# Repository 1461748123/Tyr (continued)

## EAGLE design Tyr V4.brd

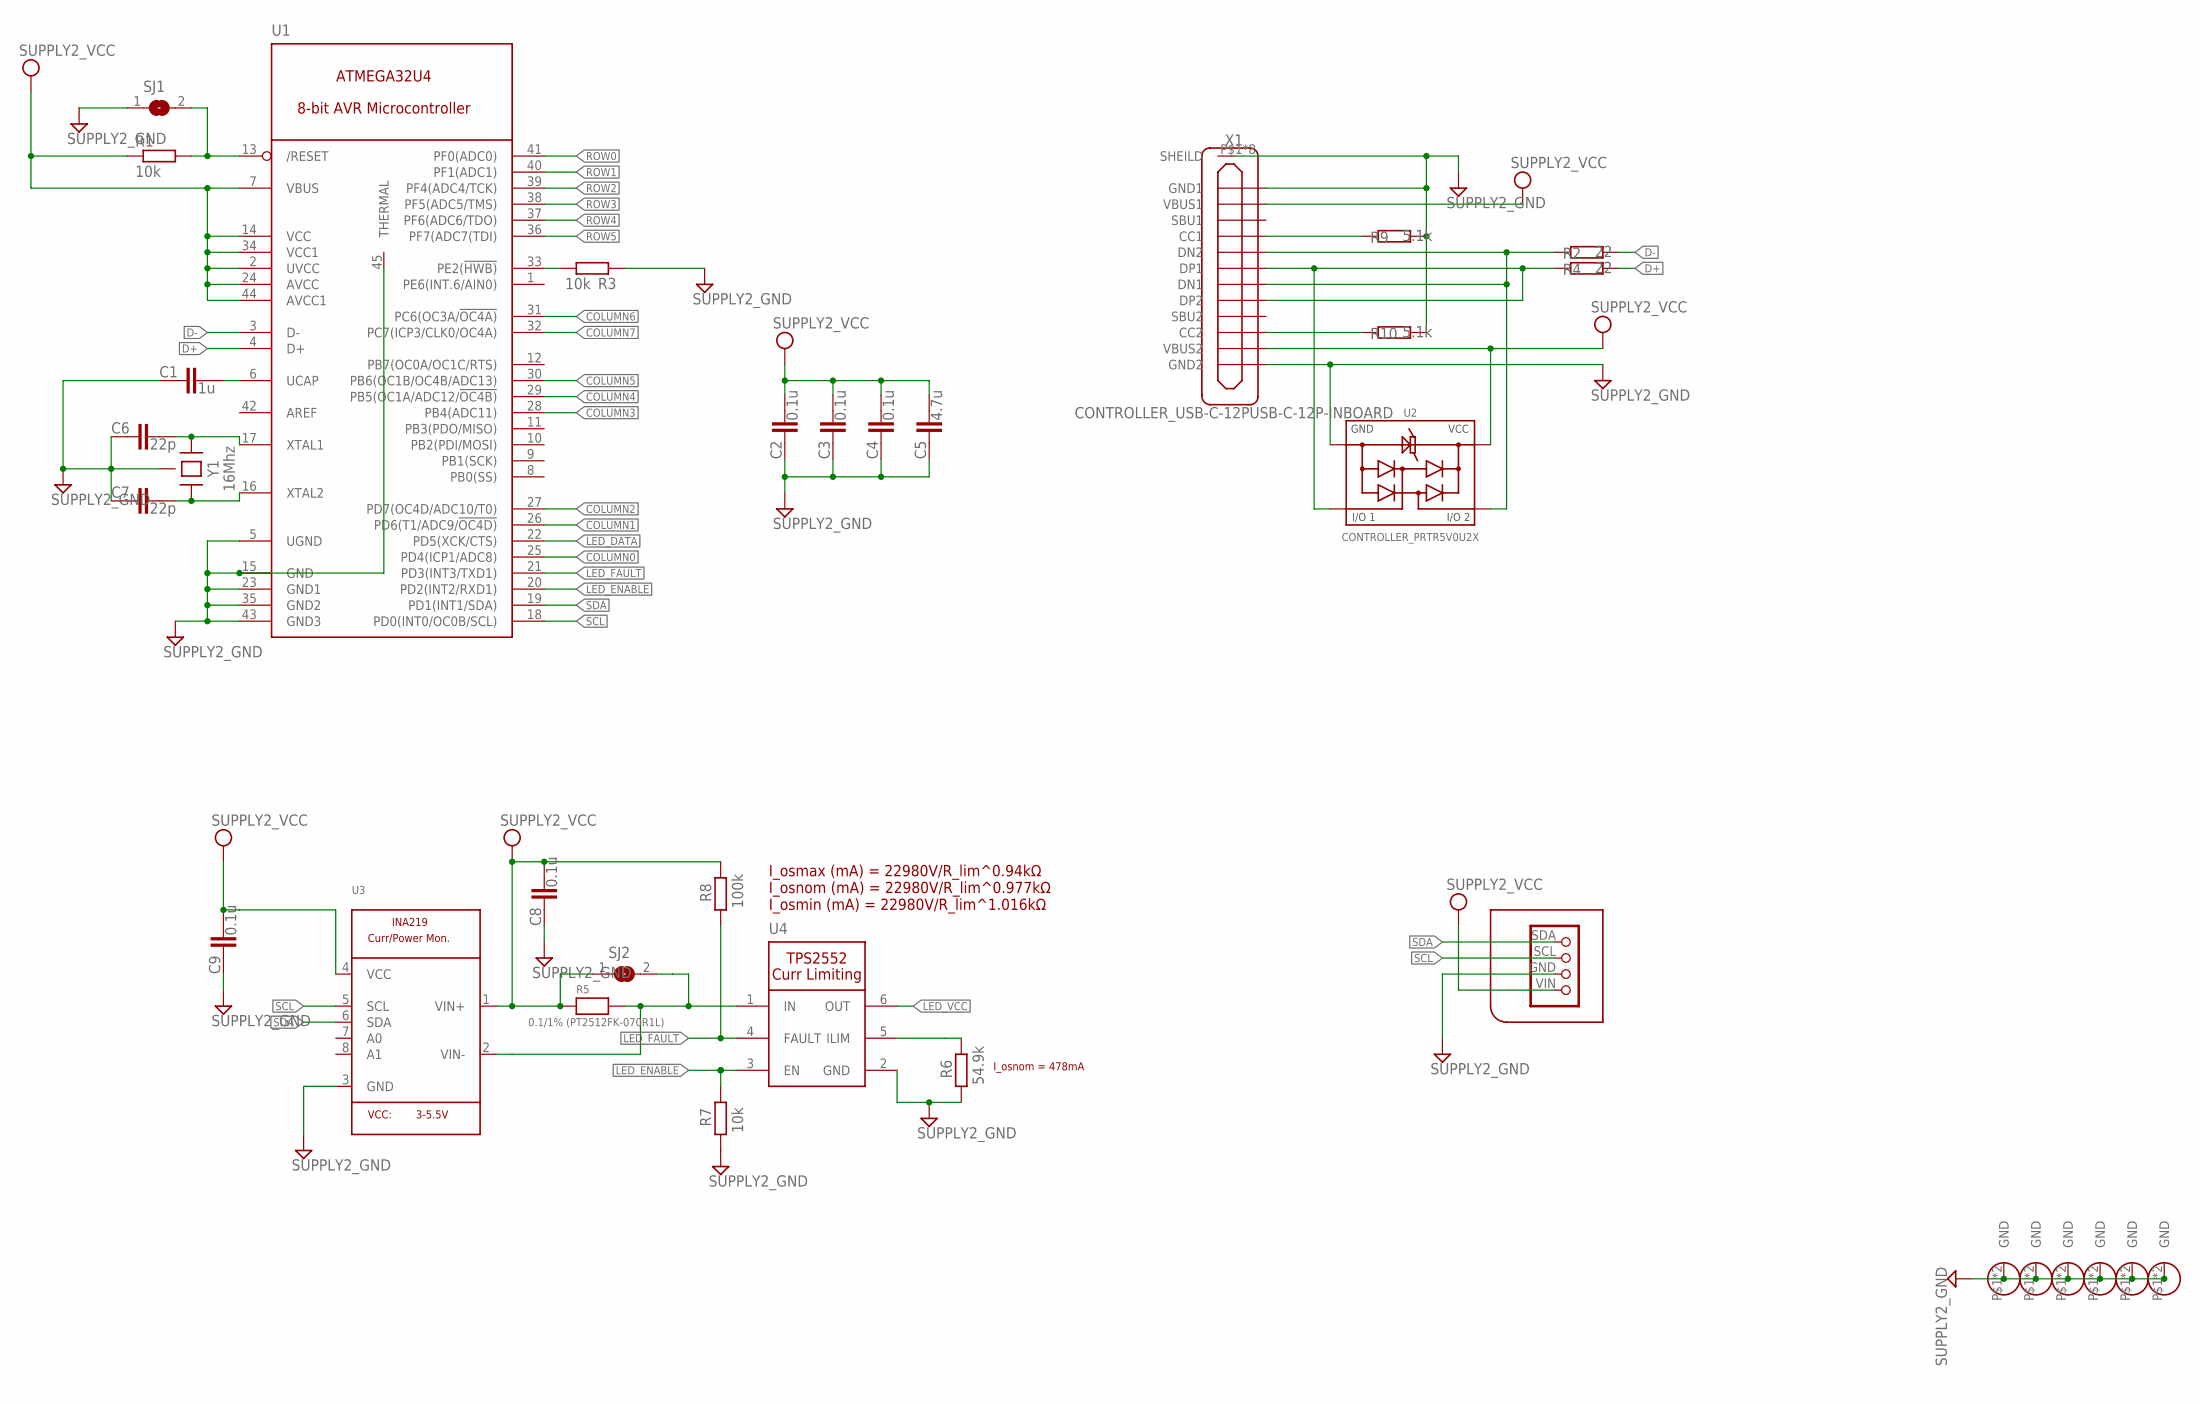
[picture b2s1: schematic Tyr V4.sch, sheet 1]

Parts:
C1: 1u; COMPONENTS_C0603
C2, C3, C4, C8, C9: 0.1u; COMPONENTS_C0603
C5: 4.7u; COMPONENTS_C0603
C6, C7: 22p; COMPONENTS_C0603
HOLE1, HOLE2, HOLE3, HOLE4, HOLE5, HOLE6: HOLE_MOUNT_HOLE; HOLE_M3_OVAL
J1: TYR_TYR_DISPLAY
R1, R3, R7: 10k; COMPONENTS_R0603
R2, R4: 22; COMPONENTS_R0603
R5: 0.1/1% (PT2512FK-070R1L); MICROBUILDER_2512
R6: 54.9k; COMPONENTS_R0603
R8: 100k; COMPONENTS_R0603
R9, R10: 5.1k; COMPONENTS_R0603
SJ1, SJ2: MICROBUILDER_SOLDERJUMPER; MICROBUILDER_SOLDERJUMPER_ARROW_NOPASTE
U1: TYR_ATMEGA32U4; TYR_QFN44-7X7
U2: CONTROLLER_PRTR5V0U2X
U3: MICROBUILDER_INA219; MICROBUILDER_SOT23-8
U4: TYR_TPS2552; TYR_SOT-23-6P
X1: CONTROLLER_USB-C-12PUSB-C-12P-INBOARD; CONTROLLER_USB-C-12P-INBOARD
Y1: 16Mhz; CONTROLLER_CRYSTAL-3.2X2.5

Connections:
COLUMN0: U1.25 (PD4(ICP1/ADC8)); also elsewhere on the board
COLUMN1: U1.26 (PD6(T1/ADC9/!OC4D)); also elsewhere on the board
COLUMN2: U1.27 (PD7(OC4D/ADC10/T0)); also elsewhere on the board
COLUMN3: U1.28 (PB4(ADC11)); also elsewhere on the board
COLUMN4: U1.29 (PB5(OC1A/ADC12/!OC4B)); also elsewhere on the board
COLUMN5: U1.30 (PB6(OC1B/OC4B/ADC13)); also elsewhere on the board
COLUMN6: U1.31 (PC6(OC3A/!OC4A)); also elsewhere on the board
COLUMN7: U1.32 (PC7(ICP3/CLK0/OC4A)); also elsewhere on the board
D+: R4.2, U1.4 (D+)
D-: R2.2, U1.3 (D-)
GND: C1.1, C2.1, C3.1, C4.1, C5.1, C6.1, C7.1, C8.1, C9.1, HOLE1.P$1, HOLE1.P$2, HOLE2.P$1, HOLE2.P$2, HOLE3.P$1, HOLE3.P$2, HOLE4.P$1, HOLE4.P$2, HOLE5.P$1, HOLE5.P$2, HOLE6.P$1, HOLE6.P$2, J1.GND (3), R3.1, R6.1, R7.1, R9.2, R10.2, SJ1.1, U1.5 (UGND), U1.15 (GND), U1.23 (GND1), U1.35 (GND2), U1.43 (GND3), U1.45 (THERMAL), U2.1, U3.3 (GND), U4.2 (GND), X1.GND1, X1.GND2, X1.P$1 (SHEILD), X1.P$2 (SHEILD), X1.P$3 (SHEILD), X1.P$4 (SHEILD), X1.P$5 (SHEILD), X1.P$6 (SHEILD), X1.P$8 (SHEILD), X1.P$9 (SHEILD), Y1.2 (GND), Y1.4 (GND); also elsewhere on the board
LED_DATA: U1.22 (PD5(XCK/CTS)); also elsewhere on the board
LED_ENABLE: R7.2, U1.20 (PD2(INT2/RXD1)), U4.3 (EN)
LED_FAULT: R8.1, U1.21 (PD3(INT3/TXD1)), U4.4 (FAULT)
LED_VCC: U4.6 (OUT); also elsewhere on the board
unnamed: R5.2, SJ2.2, U3.2 (VIN-), U4.1 (IN)
unnamed: R6.2, U4.5 (ILIM)
unnamed: R9.1, X1.CC1
unnamed: R3.2, U1.33 (PE2(!HWB))
unnamed: R2.1, U2.3, X1.DN1, X1.DN2
unnamed: R4.1, U2.2, X1.DP1, X1.DP2
unnamed: C1.2, U1.6 (UCAP)
unnamed: R10.1, X1.CC2
RESET: R1.2, SJ1.2, U1.13 (/RESET)
ROW0: U1.41 (PF0(ADC0)); also elsewhere on the board
ROW1: U1.40 (PF1(ADC1)); also elsewhere on the board
ROW2: U1.39 (PF4(ADC4/TCK)); also elsewhere on the board
ROW3: U1.38 (PF5(ADC5/TMS)); also elsewhere on the board
ROW4: U1.37 (PF6(ADC6/TDO)); also elsewhere on the board
ROW5: U1.36 (PF7(ADC7(TDI)); also elsewhere on the board
SCL: J1.SCL (2), U1.18 (PD0(INT0/OC0B/SCL)), U3.5 (SCL)
SDA: J1.SDA (1), U1.19 (PD1(INT1/SDA)), U3.6 (SDA)
VCC: C2.2, C3.2, C4.2, C5.2, C8.2, C9.2, J1.VIN (4), R1.1, R5.1, R8.2, SJ2.1, U1.2 (UVCC), U1.7 (VBUS), U1.14 (VCC), U1.24 (AVCC), U1.34 (VCC1), U1.44 (AVCC1), U2.4, U3.1 (VIN+), U3.4 (VCC), X1.VBUS1, X1.VBUS2
XTAL1: C6.2, U1.17 (XTAL1), Y1.1
XTAL2: C7.2, U1.16 (XTAL2), Y1.3 (2)

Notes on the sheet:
I_osmax (mA) = 22980V/R_lim^0.94kΩ I_osnom (mA) = 22980V/R_lim^0.977kΩ I_osmin (mA) = 22980V/R_lim^1.016kΩ
I_osnom = 478mA

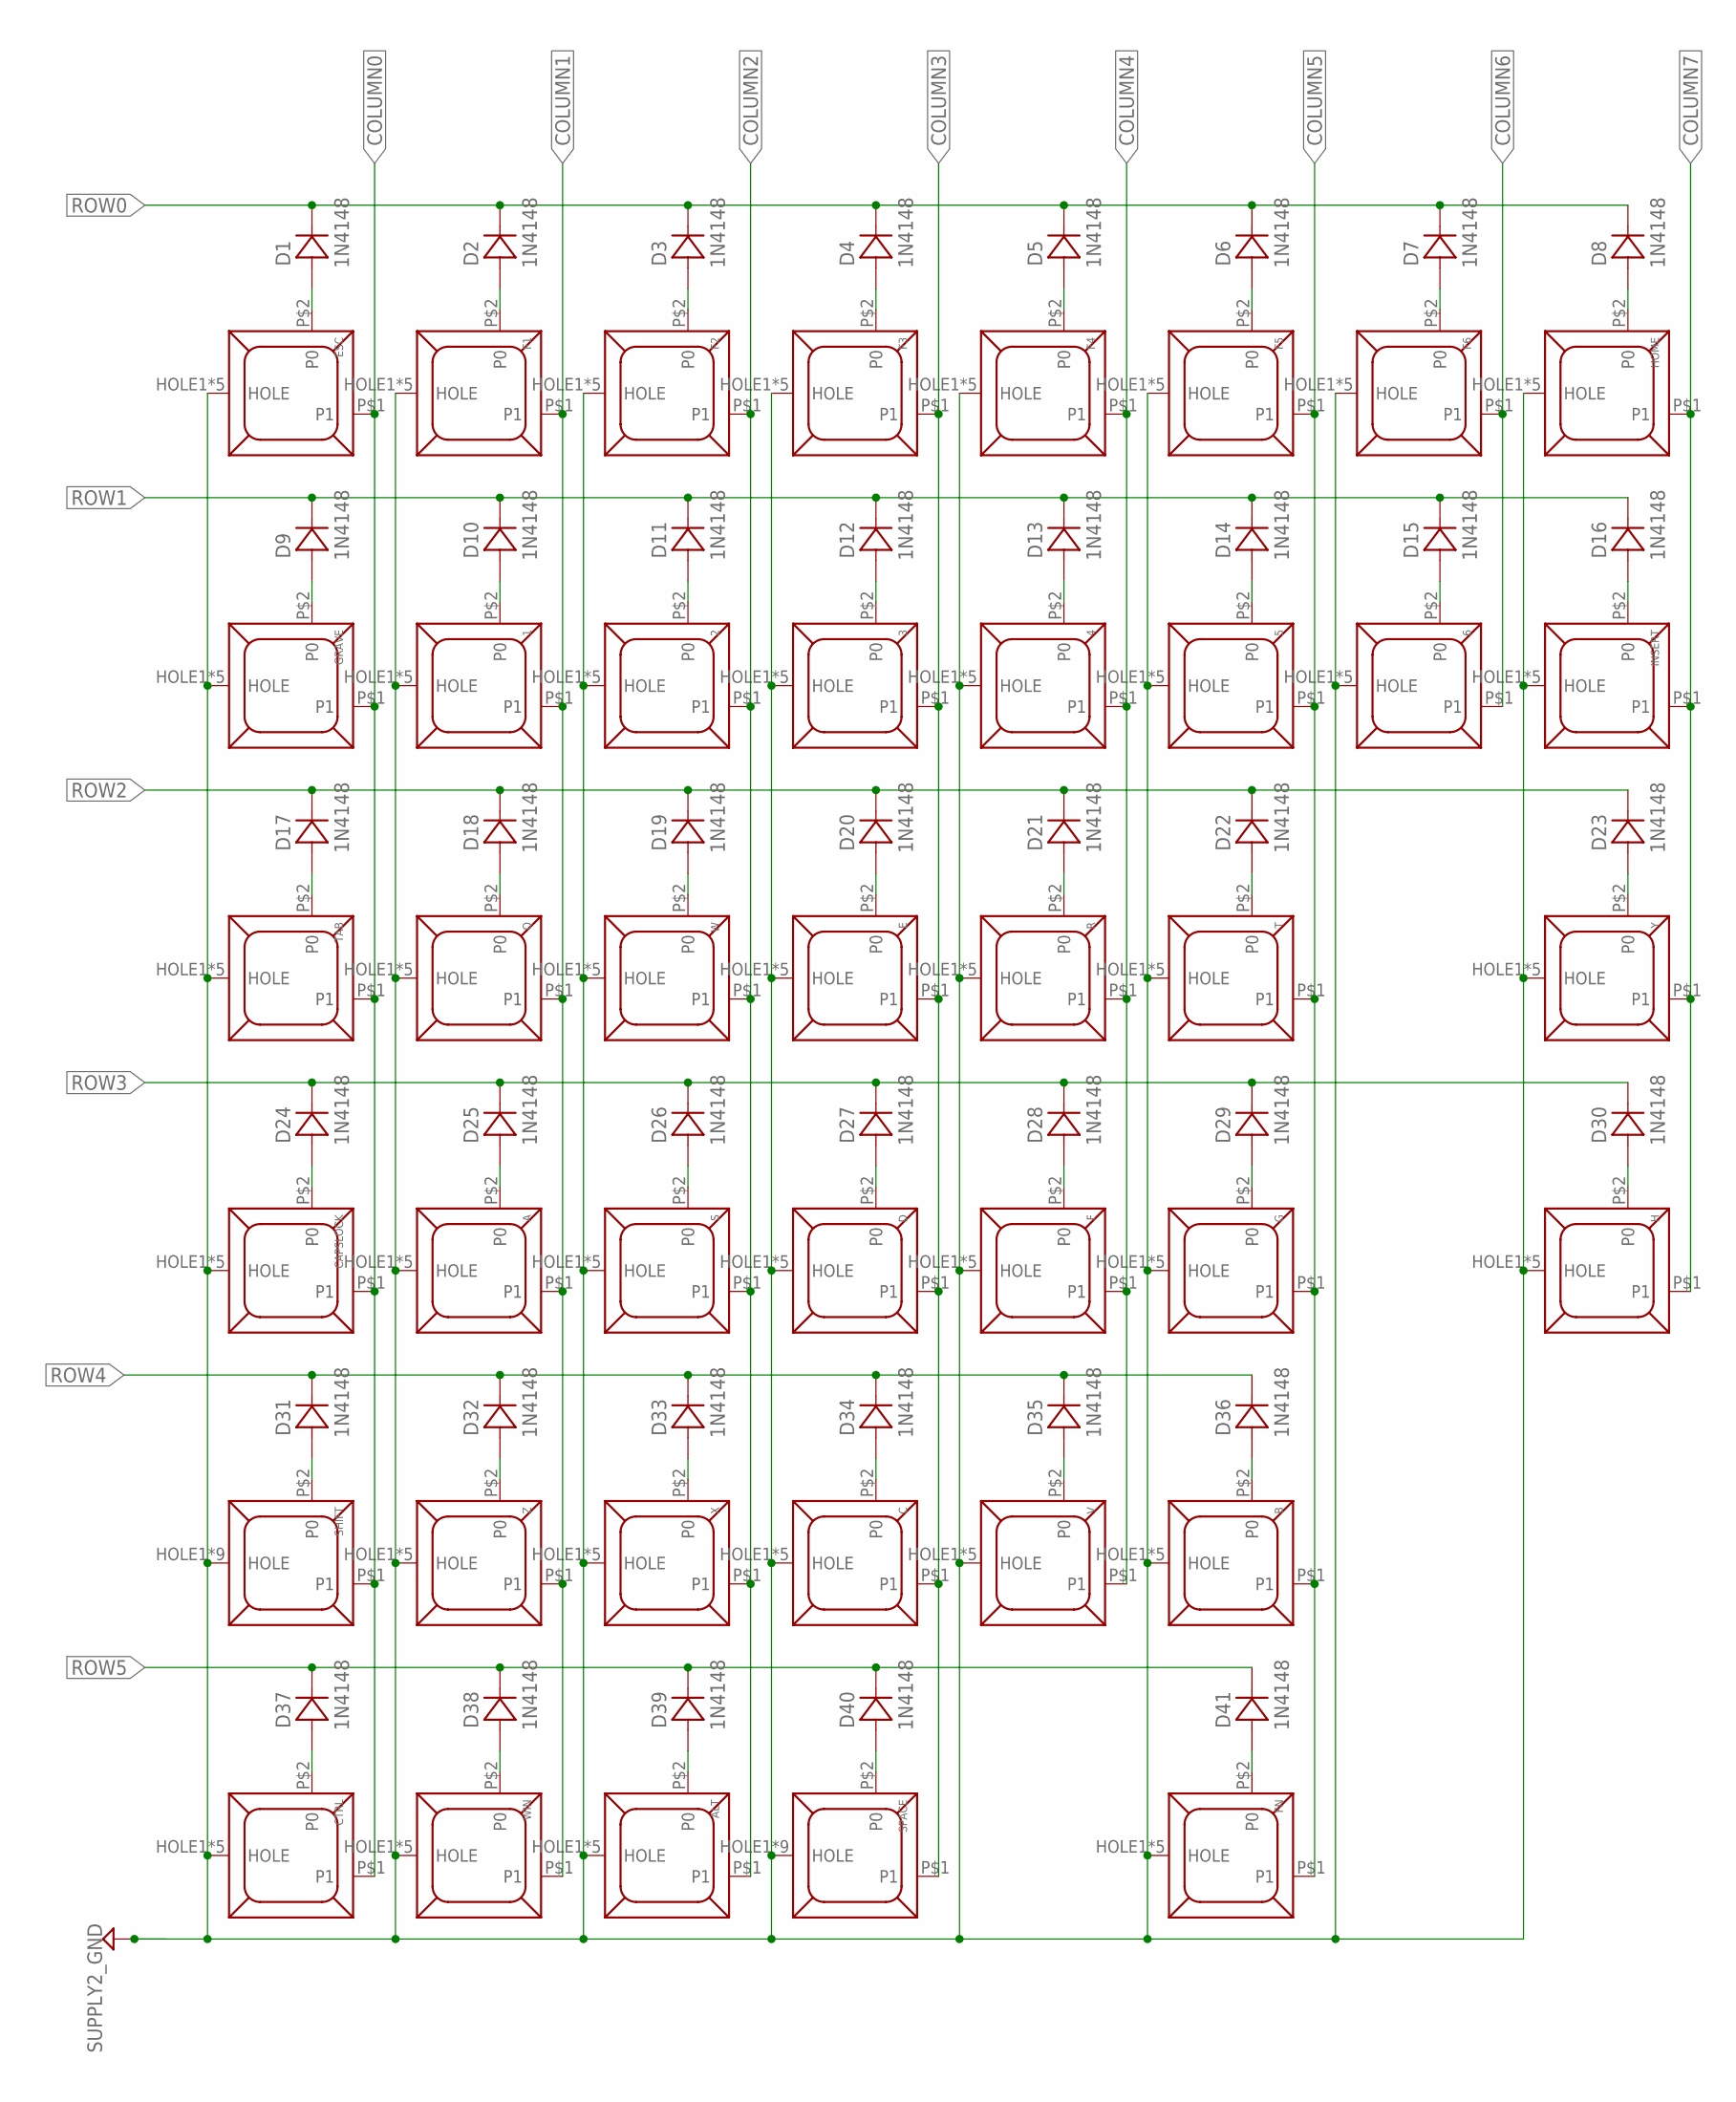
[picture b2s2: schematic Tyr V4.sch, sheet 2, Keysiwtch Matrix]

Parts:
1, 2, 3, 4, 5, 6: KEYBOARD_KEYSWITCH-MX-1U-HOTSWAP; KEYBOARD_MX-1U-HOTSWAP
A: KEYBOARD_KEYSWITCH-MX-1U-HOTSWAP; KEYBOARD_MX-1U-HOTSWAP
ALT: KEYBOARD_KEYSWITCH-MX-1U-HOTSWAP; KEYBOARD_MX-1U-HOTSWAP
B: KEYBOARD_KEYSWITCH-MX-1U-HOTSWAP; KEYBOARD_MX-1U-HOTSWAP
C: KEYBOARD_KEYSWITCH-MX-1U-HOTSWAP; KEYBOARD_MX-1U-HOTSWAP
CAPSLOCK: KEYBOARD_KEYSWITCH-MX-1U-HOTSWAPCAPSLOCK; KEYBOARD_MX-1U-HOTSWAP-CAPSLOCK
CTRL: KEYBOARD_KEYSWITCH-MX-1U-HOTSWAP; KEYBOARD_MX-1U-HOTSWAP
D: KEYBOARD_KEYSWITCH-MX-1U-HOTSWAP; KEYBOARD_MX-1U-HOTSWAP
D1, D2, D3, D4, D5, D6, D7, D8, D9, D10, D11, D12, D13, D14, D15, D16, D17, D18, D19, D20, D21, D22, D23, D24, D25, D26, D27, D28, D29, D30, D31, D32, D33, D34, D35, D36, D37, D38, D39, D40, D41: 1N4148; COMPONENTS_SOD-123
E: KEYBOARD_KEYSWITCH-MX-1U-HOTSWAP; KEYBOARD_MX-1U-HOTSWAP
ESC: KEYBOARD_KEYSWITCH-MX-1U-HOTSWAP; KEYBOARD_MX-1U-HOTSWAP
F, F1, F2, F3, F4, F5, F6: KEYBOARD_KEYSWITCH-MX-1U-HOTSWAP; KEYBOARD_MX-1U-HOTSWAP
FN: KEYBOARD_KEYSWITCH-MX-1U-HOTSWAP; KEYBOARD_MX-1U-HOTSWAP
G: KEYBOARD_KEYSWITCH-MX-1U-HOTSWAP; KEYBOARD_MX-1U-HOTSWAP
GRAVE: KEYBOARD_KEYSWITCH-MX-1U-HOTSWAP; KEYBOARD_MX-1U-HOTSWAP
H: KEYBOARD_KEYSWITCH-MX-1U-HOTSWAP; KEYBOARD_MX-1U-HOTSWAP
HOME: KEYBOARD_KEYSWITCH-MX-1U-HOTSWAP; KEYBOARD_MX-1U-HOTSWAP
INSERT: KEYBOARD_KEYSWITCH-MX-1U-HOTSWAP; KEYBOARD_MX-1U-HOTSWAP
Q: KEYBOARD_KEYSWITCH-MX-1U-HOTSWAP; KEYBOARD_MX-1U-HOTSWAP
R: KEYBOARD_KEYSWITCH-MX-1U-HOTSWAP; KEYBOARD_MX-1U-HOTSWAP
S: KEYBOARD_KEYSWITCH-MX-1U-HOTSWAP; KEYBOARD_MX-1U-HOTSWAP
SHIFT: KEYBOARD_KEYSWITCH-MX-2U-HOTSWAP; KEYBOARD_MX-2U-HOTSWAP
SPACE: KEYBOARD_KEYSWITCH-MX-2U-HOTSWAP; KEYBOARD_MX-2U-HOTSWAP
T: KEYBOARD_KEYSWITCH-MX-1U-HOTSWAP; KEYBOARD_MX-1U-HOTSWAP
TAB: KEYBOARD_KEYSWITCH-MX-1U-HOTSWAP; KEYBOARD_MX-1U-HOTSWAP
V: KEYBOARD_KEYSWITCH-MX-1U-HOTSWAP; KEYBOARD_MX-1U-HOTSWAP
W: KEYBOARD_KEYSWITCH-MX-1U-HOTSWAP; KEYBOARD_MX-1U-HOTSWAP
WIN: KEYBOARD_KEYSWITCH-MX-1U-HOTSWAP; KEYBOARD_MX-1U-HOTSWAP
X: KEYBOARD_KEYSWITCH-MX-1U-HOTSWAP; KEYBOARD_MX-1U-HOTSWAP
Y: KEYBOARD_KEYSWITCH-MX-1U-HOTSWAP; KEYBOARD_MX-1U-HOTSWAP
Z: KEYBOARD_KEYSWITCH-MX-1U-HOTSWAP; KEYBOARD_MX-1U-HOTSWAP

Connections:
COLUMN0: CAPSLOCK.P$1 (P1), CTRL.P$1 (P1), ESC.P$1 (P1), GRAVE.P$1 (P1), SHIFT.P$1 (P1), TAB.P$1 (P1); also elsewhere on the board
COLUMN1: 1.P$1 (P1), A.P$1 (P1), F1.P$1 (P1), Q.P$1 (P1), WIN.P$1 (P1), Z.P$1 (P1); also elsewhere on the board
COLUMN2: 2.P$1 (P1), ALT.P$1 (P1), F2.P$1 (P1), S.P$1 (P1), W.P$1 (P1), X.P$1 (P1); also elsewhere on the board
COLUMN3: 3.P$1 (P1), C.P$1 (P1), D.P$1 (P1), E.P$1 (P1), F3.P$1 (P1), SPACE.P$1 (P1); also elsewhere on the board
COLUMN4: 4.P$1 (P1), F.P$1 (P1), F4.P$1 (P1), R.P$1 (P1), V.P$1 (P1); also elsewhere on the board
COLUMN5: 5.P$1 (P1), B.P$1 (P1), F5.P$1 (P1), FN.P$1 (P1), G.P$1 (P1), T.P$1 (P1); also elsewhere on the board
COLUMN6: 6.P$1 (P1), F6.P$1 (P1); also elsewhere on the board
COLUMN7: H.P$1 (P1), HOME.P$1 (P1), INSERT.P$1 (P1), Y.P$1 (P1); also elsewhere on the board
GND: 1.HOLE1 (HOLE), 1.HOLE2 (HOLE), 1.HOLE3 (HOLE), 1.HOLE4 (HOLE), 1.HOLE5 (HOLE), 2.HOLE1 (HOLE), 2.HOLE2 (HOLE), 2.HOLE3 (HOLE), 2.HOLE4 (HOLE), 2.HOLE5 (HOLE), 3.HOLE1 (HOLE), 3.HOLE2 (HOLE), 3.HOLE3 (HOLE), 3.HOLE4 (HOLE), 3.HOLE5 (HOLE), 4.HOLE1 (HOLE), 4.HOLE2 (HOLE), 4.HOLE3 (HOLE), 4.HOLE4 (HOLE), 4.HOLE5 (HOLE), 5.HOLE1 (HOLE), 5.HOLE2 (HOLE), 5.HOLE3 (HOLE), 5.HOLE4 (HOLE), 5.HOLE5 (HOLE), 6.HOLE1 (HOLE), 6.HOLE2 (HOLE), 6.HOLE3 (HOLE), 6.HOLE4 (HOLE), 6.HOLE5 (HOLE), A.HOLE1 (HOLE), A.HOLE2 (HOLE), A.HOLE3 (HOLE), A.HOLE4 (HOLE), A.HOLE5 (HOLE), ALT.HOLE1 (HOLE), ALT.HOLE2 (HOLE), ALT.HOLE3 (HOLE), ALT.HOLE4 (HOLE), ALT.HOLE5 (HOLE), B.HOLE1 (HOLE), B.HOLE2 (HOLE), B.HOLE3 (HOLE), B.HOLE4 (HOLE), B.HOLE5 (HOLE), C.HOLE1 (HOLE), C.HOLE2 (HOLE), C.HOLE3 (HOLE), C.HOLE4 (HOLE), C.HOLE5 (HOLE), CAPSLOCK.HOLE1 (HOLE), CAPSLOCK.HOLE2 (HOLE), CAPSLOCK.HOLE3 (HOLE), CAPSLOCK.HOLE4 (HOLE), CAPSLOCK.HOLE5 (HOLE), CTRL.HOLE1 (HOLE), CTRL.HOLE2 (HOLE), CTRL.HOLE3 (HOLE), CTRL.HOLE4 (HOLE), CTRL.HOLE5 (HOLE), D.HOLE1 (HOLE), D.HOLE2 (HOLE), D.HOLE3 (HOLE), D.HOLE4 (HOLE), D.HOLE5 (HOLE), E.HOLE1 (HOLE), E.HOLE2 (HOLE), E.HOLE3 (HOLE), E.HOLE4 (HOLE), E.HOLE5 (HOLE), ESC.HOLE1 (HOLE), ESC.HOLE2 (HOLE), ESC.HOLE3 (HOLE), ESC.HOLE4 (HOLE), ESC.HOLE5 (HOLE), F.HOLE1 (HOLE), F.HOLE2 (HOLE), F.HOLE3 (HOLE), F.HOLE4 (HOLE), F.HOLE5 (HOLE), F1.HOLE1 (HOLE), F1.HOLE2 (HOLE), F1.HOLE3 (HOLE), F1.HOLE4 (HOLE), F1.HOLE5 (HOLE), F2.HOLE1 (HOLE), F2.HOLE2 (HOLE), F2.HOLE3 (HOLE), F2.HOLE4 (HOLE), F2.HOLE5 (HOLE), F3.HOLE1 (HOLE), F3.HOLE2 (HOLE), F3.HOLE3 (HOLE), F3.HOLE4 (HOLE), F3.HOLE5 (HOLE), F4.HOLE1 (HOLE), F4.HOLE2 (HOLE), F4.HOLE3 (HOLE), F4.HOLE4 (HOLE), F4.HOLE5 (HOLE), F5.HOLE1 (HOLE), F5.HOLE2 (HOLE), F5.HOLE3 (HOLE), F5.HOLE4 (HOLE), F5.HOLE5 (HOLE), F6.HOLE1 (HOLE), F6.HOLE2 (HOLE), F6.HOLE3 (HOLE), F6.HOLE4 (HOLE), F6.HOLE5 (HOLE), FN.HOLE1 (HOLE), FN.HOLE2 (HOLE), FN.HOLE3 (HOLE), FN.HOLE4 (HOLE), FN.HOLE5 (HOLE), G.HOLE1 (HOLE), G.HOLE2 (HOLE), G.HOLE3 (HOLE), G.HOLE4 (HOLE), G.HOLE5 (HOLE), GRAVE.HOLE1 (HOLE), GRAVE.HOLE2 (HOLE), GRAVE.HOLE3 (HOLE), GRAVE.HOLE4 (HOLE), GRAVE.HOLE5 (HOLE), H.HOLE1 (HOLE), H.HOLE2 (HOLE), H.HOLE3 (HOLE), H.HOLE4 (HOLE), H.HOLE5 (HOLE), HOME.HOLE1 (HOLE), HOME.HOLE2 (HOLE), HOME.HOLE3 (HOLE), HOME.HOLE4 (HOLE), HOME.HOLE5 (HOLE), INSERT.HOLE1 (HOLE), INSERT.HOLE2 (HOLE), INSERT.HOLE3 (HOLE), INSERT.HOLE4 (HOLE), INSERT.HOLE5 (HOLE), Q.HOLE1 (HOLE), Q.HOLE2 (HOLE), Q.HOLE3 (HOLE), Q.HOLE4 (HOLE), Q.HOLE5 (HOLE), R.HOLE1 (HOLE), R.HOLE2 (HOLE), R.HOLE3 (HOLE), R.HOLE4 (HOLE), R.HOLE5 (HOLE), S.HOLE1 (HOLE), S.HOLE2 (HOLE), S.HOLE3 (HOLE), S.HOLE4 (HOLE), S.HOLE5 (HOLE), SHIFT.HOLE1 (HOLE), SHIFT.HOLE2 (HOLE), SHIFT.HOLE3 (HOLE), SHIFT.HOLE4 (HOLE), SHIFT.HOLE5 (HOLE), SHIFT.HOLE6 (HOLE), SHIFT.HOLE7 (HOLE), SHIFT.HOLE8 (HOLE), SHIFT.HOLE9 (HOLE), SPACE.HOLE1 (HOLE), SPACE.HOLE2 (HOLE), SPACE.HOLE3 (HOLE), SPACE.HOLE4 (HOLE), SPACE.HOLE5 (HOLE), SPACE.HOLE6 (HOLE), SPACE.HOLE7 (HOLE), SPACE.HOLE8 (HOLE), SPACE.HOLE9 (HOLE), T.HOLE1 (HOLE), T.HOLE2 (HOLE), T.HOLE3 (HOLE), T.HOLE4 (HOLE), T.HOLE5 (HOLE), TAB.HOLE1 (HOLE), TAB.HOLE2 (HOLE), TAB.HOLE3 (HOLE), TAB.HOLE4 (HOLE), TAB.HOLE5 (HOLE), V.HOLE1 (HOLE), V.HOLE2 (HOLE), V.HOLE3 (HOLE), V.HOLE4 (HOLE), V.HOLE5 (HOLE), W.HOLE1 (HOLE), W.HOLE2 (HOLE), W.HOLE3 (HOLE), W.HOLE4 (HOLE), W.HOLE5 (HOLE), WIN.HOLE1 (HOLE), WIN.HOLE2 (HOLE), WIN.HOLE3 (HOLE), WIN.HOLE4 (HOLE), WIN.HOLE5 (HOLE), X.HOLE1 (HOLE), X.HOLE2 (HOLE), X.HOLE3 (HOLE), X.HOLE4 (HOLE), X.HOLE5 (HOLE), Y.HOLE1 (HOLE), Y.HOLE2 (HOLE), Y.HOLE3 (HOLE), Y.HOLE4 (HOLE), Y.HOLE5 (HOLE), Z.HOLE1 (HOLE), Z.HOLE2 (HOLE), Z.HOLE3 (HOLE), Z.HOLE4 (HOLE), Z.HOLE5 (HOLE); also elsewhere on the board
unnamed: 1.P$2 (P0), D10.A
unnamed: D1.A, ESC.P$2 (P0)
unnamed: D2.A, F1.P$2 (P0)
unnamed: D3.A, F2.P$2 (P0)
unnamed: D4.A, F3.P$2 (P0)
unnamed: D5.A, F4.P$2 (P0)
unnamed: D6.A, F5.P$2 (P0)
unnamed: D7.A, F6.P$2 (P0)
unnamed: D8.A, HOME.P$2 (P0)
unnamed: D16.A, INSERT.P$2 (P0)
unnamed: 6.P$2 (P0), D15.A
unnamed: 5.P$2 (P0), D14.A
unnamed: 4.P$2 (P0), D13.A
unnamed: 3.P$2 (P0), D12.A
unnamed: 2.P$2 (P0), D11.A
unnamed: D9.A, GRAVE.P$2 (P0)
unnamed: D23.A, Y.P$2 (P0)
unnamed: D22.A, T.P$2 (P0)
unnamed: D21.A, R.P$2 (P0)
unnamed: D20.A, E.P$2 (P0)
unnamed: D19.A, W.P$2 (P0)
unnamed: D17.A, TAB.P$2 (P0)
unnamed: CAPSLOCK.P$2 (P0), D24.A
unnamed: A.P$2 (P0), D25.A
unnamed: D26.A, S.P$2 (P0)
unnamed: D.P$2 (P0), D27.A
unnamed: D28.A, F.P$2 (P0)
unnamed: D29.A, G.P$2 (P0)
unnamed: D30.A, H.P$2 (P0)
unnamed: B.P$2 (P0), D36.A
unnamed: C.P$2 (P0), D34.A
unnamed: D33.A, X.P$2 (P0)
unnamed: D32.A, Z.P$2 (P0)
unnamed: D31.A, SHIFT.P$2 (P0)
unnamed: CTRL.P$2 (P0), D37.A
unnamed: D38.A, WIN.P$2 (P0)
unnamed: ALT.P$2 (P0), D39.A
unnamed: D40.A, SPACE.P$2 (P0)
unnamed: D41.A, FN.P$2 (P0)
unnamed: D35.A, V.P$2 (P0)
unnamed: D18.A, Q.P$2 (P0)
ROW0: D1.C, D2.C, D3.C, D4.C, D5.C, D6.C, D7.C, D8.C; also elsewhere on the board
ROW1: D9.C, D10.C, D11.C, D12.C, D13.C, D14.C, D15.C, D16.C; also elsewhere on the board
ROW2: D17.C, D18.C, D19.C, D20.C, D21.C, D22.C, D23.C; also elsewhere on the board
ROW3: D24.C, D25.C, D26.C, D27.C, D28.C, D29.C, D30.C; also elsewhere on the board
ROW4: D31.C, D32.C, D33.C, D34.C, D35.C, D36.C; also elsewhere on the board
ROW5: D37.C, D38.C, D39.C, D40.C, D41.C; also elsewhere on the board

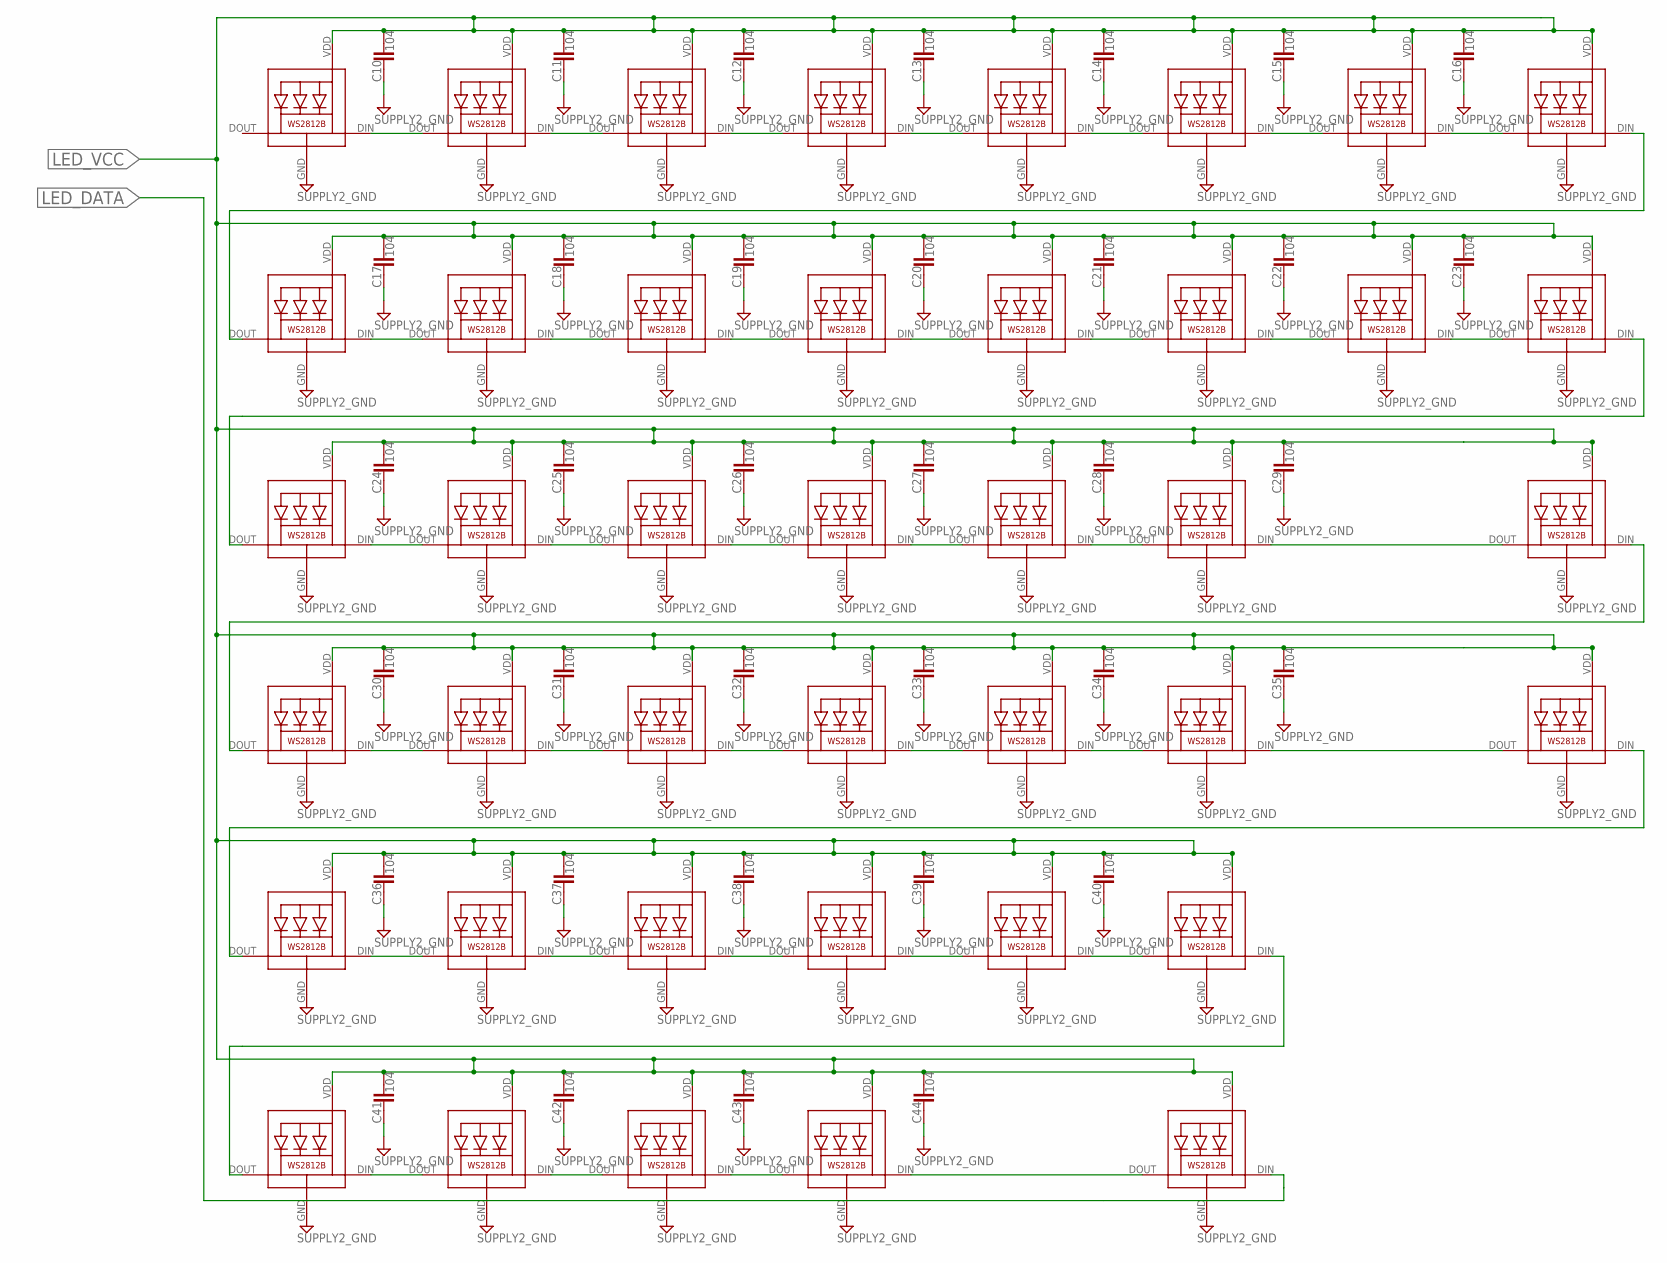
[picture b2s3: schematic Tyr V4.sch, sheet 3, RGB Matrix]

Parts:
C10, C11, C12, C13, C14, C15, C16, C17, C18, C19, C20, C21, C22, C23, C24, C25, C26, C27, C28, C29, C30, C31, C32, C33, C34, C35, C36, C37, C38, C39, C40, C41, C42, C43, C44: 104; COMPONENTS_C0603
LED1, LED2, LED3, LED4, LED5, LED6, LED7, LED8, LED9, LED10, LED11, LED12, LED13, LED14, LED15, LED16, LED17, LED18, LED19, LED20, LED21, LED22, LED23, LED24, LED25, LED26, LED27, LED28, LED29, LED30, LED31, LED32, LED33, LED34, LED35, LED36, LED37, LED38, LED39, LED40, LED41: TYR_WS2812B_3528_REVERS-MOUNT

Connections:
GND: C10.1, C11.1, C12.1, C13.1, C14.1, C15.1, C16.1, C17.1, C18.1, C19.1, C20.1, C21.1, C22.1, C23.1, C24.1, C25.1, C26.1, C27.1, C28.1, C29.1, C30.1, C31.1, C32.1, C33.1, C34.1, C35.1, C36.1, C37.1, C38.1, C39.1, C40.1, C41.1, C42.1, C43.1, C44.1, LED1.GND, LED2.GND, LED3.GND, LED4.GND, LED5.GND, LED6.GND, LED7.GND, LED8.GND, LED9.GND, LED10.GND, LED11.GND, LED12.GND, LED13.GND, LED14.GND, LED15.GND, LED16.GND, LED17.GND, LED18.GND, LED19.GND, LED20.GND, LED21.GND, LED22.GND, LED23.GND, LED24.GND, LED25.GND, LED26.GND, LED27.GND, LED28.GND, LED29.GND, LED30.GND, LED31.GND, LED32.GND, LED33.GND, LED34.GND, LED35.GND, LED36.GND, LED37.GND, LED38.GND, LED39.GND, LED40.GND, LED41.GND; also elsewhere on the board
LED_DATA: LED41.DIN (DI); also elsewhere on the board
LED_VCC: C10.2, C11.2, C12.2, C13.2, C14.2, C15.2, C16.2, C17.2, C18.2, C19.2, C20.2, C21.2, C22.2, C23.2, C24.2, C25.2, C26.2, C27.2, C28.2, C29.2, C30.2, C31.2, C32.2, C33.2, C34.2, C35.2, C36.2, C37.2, C38.2, C39.2, C40.2, C41.2, C42.2, C43.2, C44.2, LED1.VDD, LED2.VDD, LED3.VDD, LED4.VDD, LED5.VDD, LED6.VDD, LED7.VDD, LED8.VDD, LED9.VDD, LED10.VDD, LED11.VDD, LED12.VDD, LED13.VDD, LED14.VDD, LED15.VDD, LED16.VDD, LED17.VDD, LED18.VDD, LED19.VDD, LED20.VDD, LED21.VDD, LED22.VDD, LED23.VDD, LED24.VDD, LED25.VDD, LED26.VDD, LED27.VDD, LED28.VDD, LED29.VDD, LED30.VDD, LED31.VDD, LED32.VDD, LED33.VDD, LED34.VDD, LED35.VDD, LED36.VDD, LED37.VDD, LED38.VDD, LED39.VDD, LED40.VDD, LED41.VDD; also elsewhere on the board
unnamed: LED40.DIN (DI), LED41.DOUT (DO)
unnamed: LED39.DIN (DI), LED40.DOUT (DO)
unnamed: LED38.DIN (DI), LED39.DOUT (DO)
unnamed: LED37.DIN (DI), LED38.DOUT (DO)
unnamed: LED36.DIN (DI), LED37.DOUT (DO)
unnamed: LED35.DIN (DI), LED36.DOUT (DO)
unnamed: LED34.DIN (DI), LED35.DOUT (DO)
unnamed: LED33.DIN (DI), LED34.DOUT (DO)
unnamed: LED32.DIN (DI), LED33.DOUT (DO)
unnamed: LED31.DIN (DI), LED32.DOUT (DO)
unnamed: LED30.DIN (DI), LED31.DOUT (DO)
unnamed: LED29.DIN (DI), LED30.DOUT (DO)
unnamed: LED28.DIN (DI), LED29.DOUT (DO)
unnamed: LED27.DIN (DI), LED28.DOUT (DO)
unnamed: LED26.DIN (DI), LED27.DOUT (DO)
unnamed: LED25.DIN (DI), LED26.DOUT (DO)
unnamed: LED24.DIN (DI), LED25.DOUT (DO)
unnamed: LED23.DIN (DI), LED24.DOUT (DO)
unnamed: LED22.DIN (DI), LED23.DOUT (DO)
unnamed: LED21.DIN (DI), LED22.DOUT (DO)
unnamed: LED20.DIN (DI), LED21.DOUT (DO)
unnamed: LED19.DIN (DI), LED20.DOUT (DO)
unnamed: LED18.DIN (DI), LED19.DOUT (DO)
unnamed: LED17.DIN (DI), LED18.DOUT (DO)
unnamed: LED16.DIN (DI), LED17.DOUT (DO)
unnamed: LED15.DIN (DI), LED16.DOUT (DO)
unnamed: LED14.DIN (DI), LED15.DOUT (DO)
unnamed: LED13.DIN (DI), LED14.DOUT (DO)
unnamed: LED12.DIN (DI), LED13.DOUT (DO)
unnamed: LED11.DIN (DI), LED12.DOUT (DO)
unnamed: LED10.DIN (DI), LED11.DOUT (DO)
unnamed: LED9.DIN (DI), LED10.DOUT (DO)
unnamed: LED8.DIN (DI), LED9.DOUT (DO)
unnamed: LED7.DIN (DI), LED8.DOUT (DO)
unnamed: LED6.DIN (DI), LED7.DOUT (DO)
unnamed: LED5.DIN (DI), LED6.DOUT (DO)
unnamed: LED4.DIN (DI), LED5.DOUT (DO)
unnamed: LED3.DIN (DI), LED4.DOUT (DO)
unnamed: LED2.DIN (DI), LED3.DOUT (DO)
unnamed: LED1.DIN (DI), LED2.DOUT (DO)

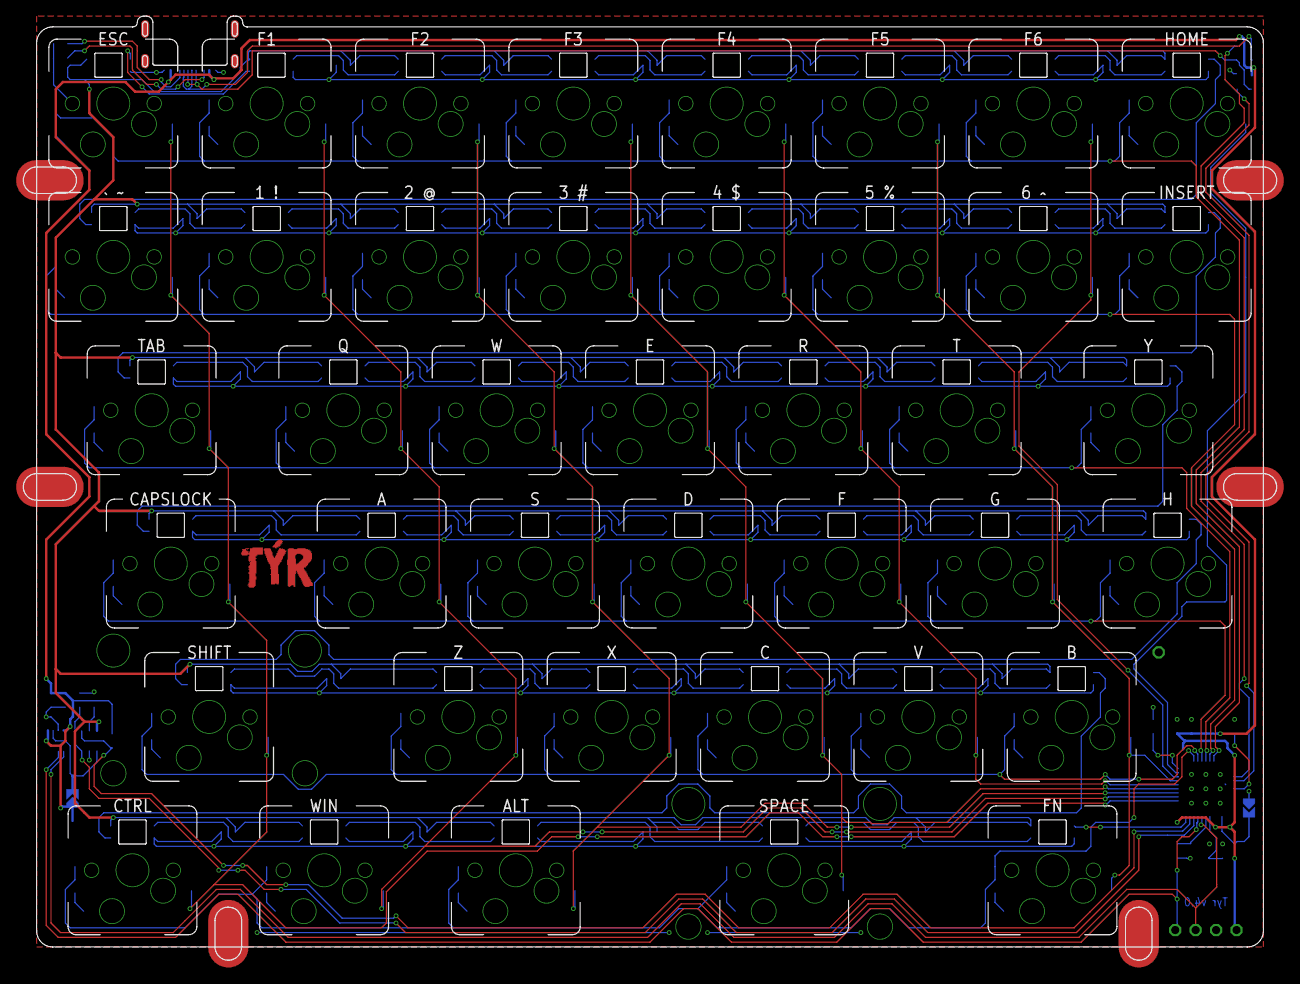
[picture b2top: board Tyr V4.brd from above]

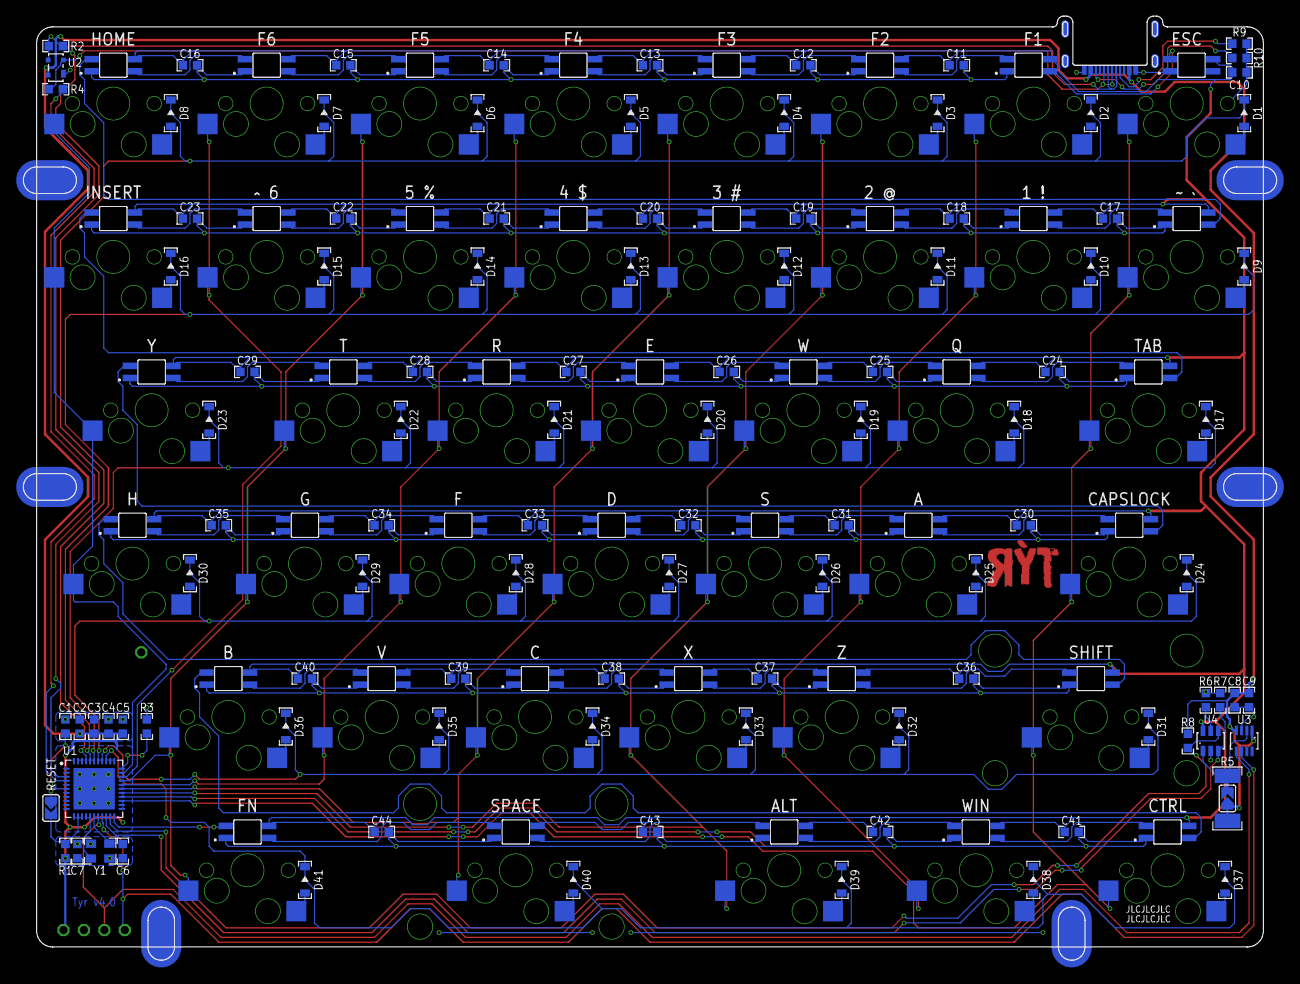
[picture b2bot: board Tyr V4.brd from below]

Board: 2 copper layers, 155.7 x 117.3 mm, 192 parts (144 on the bottom side), 116 nets.

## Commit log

2019-10-24 Update pads
2019-10-25 Added Type-C CC pulldown resistors
2019-10-25 Remove version prefix
2019-10-25 Using managed library
2019-10-28 Updated Kailh hotswap socket footprint
2019-10-29 Added usb hub
2019-10-30 Move layout
2019-10-31 Initial
2019-11-01 Layout
2019-11-05 Fix current monitoring & added I2C FRAM
2019-11-05 Y branching & renumber
2019-11-05 More Y branching
2019-11-05 Remove uneccessary power to I2C
2019-11-05 Y branching
2019-11-05 Ground plane under STM32
2019-11-05 Update logo
2019-11-06 Update trace width
2019-11-06 Update display module
2019-11-07 Hide inner layer from lagacy 4 layer board
2019-11-10 USB-C shield RC filter
2019-11-13 Update library
2019-11-13 Remove bottom outer ring
2019-11-15 Rev0.5
2019-11-15 Update dimensions of mount holes
2019-11-20 Migrate to new library
